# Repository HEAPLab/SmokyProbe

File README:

# SmokyProbe

Firmware
========

Project related to the firmware for the STM32-NUCLEO G071RB board, for sampling
the SmokyProbe on-board sensors via I2C.

SmokyProbe library (libsmokyprobe)
==================================

Host-side library for communicating with the STM32-NUCLEO board via serial interface.

Tools
=====

Host-side programs implementing specific reading functionalities.

Troubleshooting
===============

- If you have problems in tty communication with the device try the following
  stty settings:

	stty -F /dev/ttyACM0 -hupcl brkint ignpar -icrnl -ixon -opost -onlcr
	-isig -icanon -iexten -echo -echoe -echok -echoctl -echoke

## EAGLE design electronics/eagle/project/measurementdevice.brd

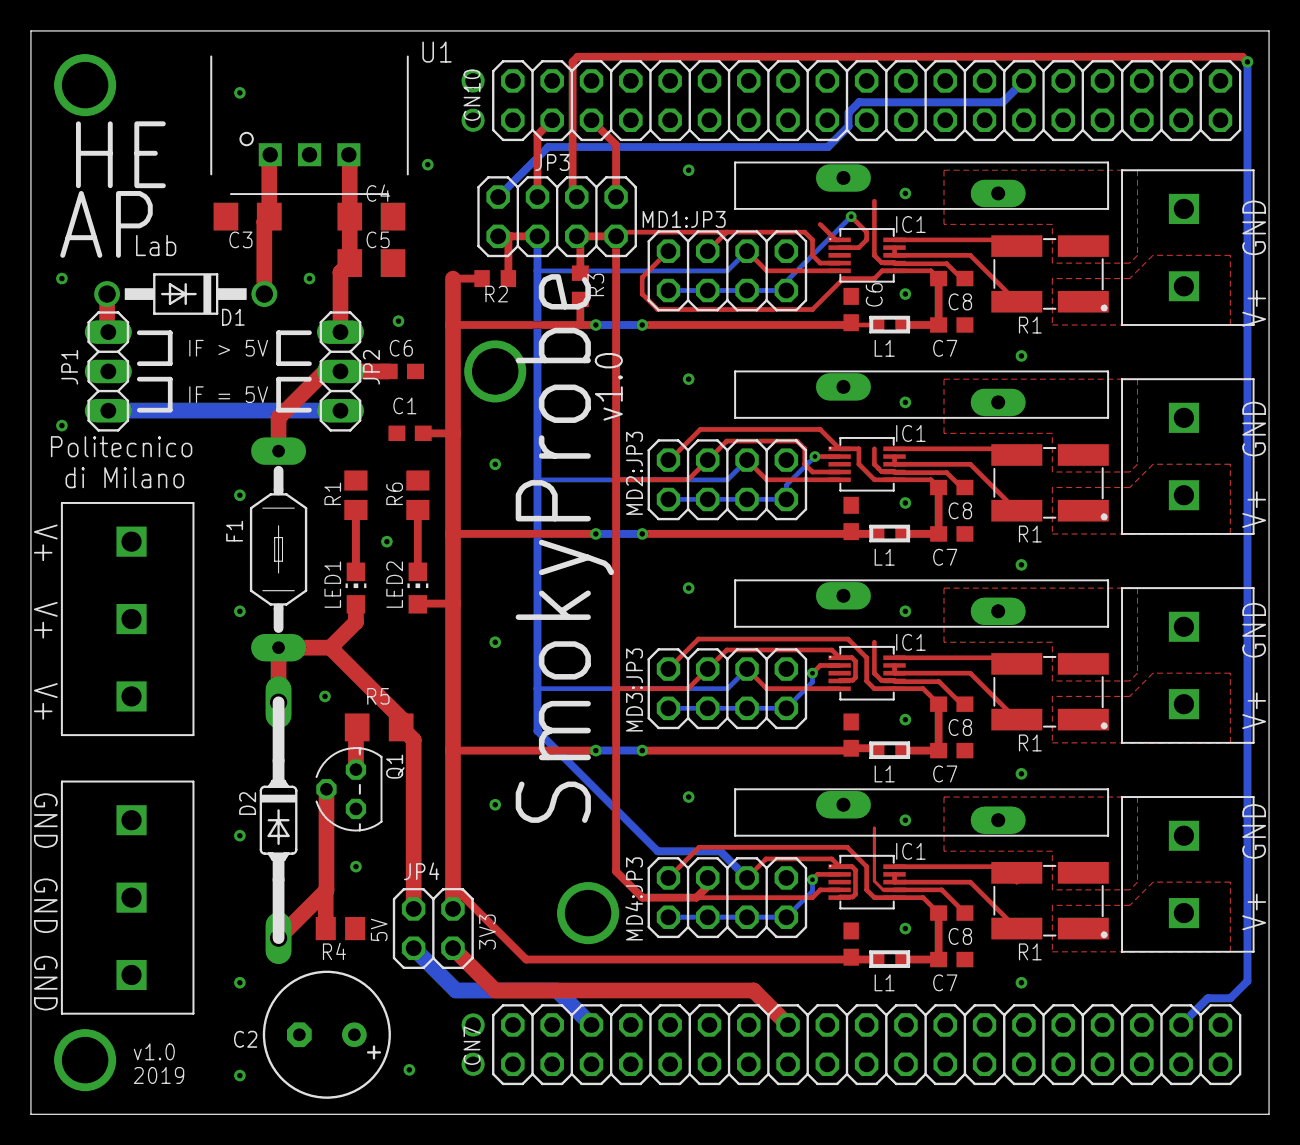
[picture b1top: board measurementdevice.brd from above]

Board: 4 copper layers, 80.0 x 70.0 mm, 63 parts (0 on the bottom side), 45 nets.

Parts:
C1: 1uF; C0603
C2: 100uF; E3,5-8
C3, C4, C5: 10uF; C1206
C6: 0.1uF; C0603
CN7, CN10: 2X19
D1: 1N5819; DO41-10
D2: BZD23C5V6; SOD81-ED
F1: 1.3A; LITTLEFUSE
JP1, JP2: 1X03
JP3: 2X04
JP4: 2X02
LED1, LED2: GREEN; CHIP-LED0805
MD1:C6, MD2:C6, MD3:C6, MD4:C6: 1uF; C0603
MD1:C7, MD2:C7, MD3:C7, MD4:C7: 0.1uF; C0603
MD1:C8, MD2:C8, MD3:C8, MD4:C8: 0.01uF; C0603
MD1:F1, MD2:F1, MD3:F1, MD4:F1: RUEF900
MD1:IC1, MD2:IC1, MD3:IC1, MD4:IC1: VSSOP10
MD1:JP3, MD2:JP3, MD3:JP3, MD4:JP3: 2X04
MD1:L1, MD2:L1, MD3:L1, MD4:L1: Ferrite Bead; 0603
MD1:R1, MD2:R1, MD3:R1, MD4:R1: 1224
MD1:X1, MD2:X1, MD3:X1, MD4:X1: PT1.5/3-50H-2
Q1: TN0604N3; TO-92
R1: 240; R0805
R2, R3: 3.9k; R0603
R4: 1k; R0805
R5: 5; R1206
R6: 100; R0805
U1: VX7805-1000; VX78-1000
X1, X2: PT1.5/3-50H-3

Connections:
3V3: CN7.16, JP4.3
+3V3: C1.2, JP4.4, LED2.A, MD1:C6.2, MD1:L1.N1, MD2:C6.2, MD2:L1.N1, MD3:C6.2, MD3:L1.N1, MD4:C6.2, MD4:L1.N1, R2.2, R3.2
+5V: D2.C, F1.2, JP4.2, LED1.A, R5.2
E5V: CN7.6, JP4.1
GND: C1.1, C2.-, C3.2, C4.2, C5.2, C6.2, CN7.8, CN7.19, CN7.20, CN7.22, CN10.9, CN10.20, MD1:C6.1, MD1:C7.1, MD1:C8.1, MD1:IC1.1, MD1:IC1.7, MD1:JP3.8, MD1:X1.P$1, MD2:C6.1, MD2:C7.1, MD2:C8.1, MD2:IC1.7, MD2:JP3.8, MD2:X1.P$1, MD3:C6.1, MD3:C7.1, MD3:C8.1, MD3:IC1.7, MD3:JP3.8, MD3:X1.P$1, MD4:C6.1, MD4:C7.1, MD4:C8.1, MD4:IC1.7, MD4:JP3.8, MD4:X1.P$1, Q1.1, R1.1, R4.1, R6.1, U1.P$2, X2.P$1, X2.P$2, X2.P$3
MD1:3V3_FILTERED: MD1:C7.2, MD1:C8.2, MD1:IC1.6, MD1:JP3.2, MD1:L1.N2
MD1:A0: MD1:IC1.2, MD1:JP3.1, MD1:JP3.3, MD1:JP3.5, MD1:JP3.7
MD1:PWR_IN: MD1:F1.P$2, MD1:R1.2
MD1:PWR_OUT: MD1:R1.1, MD1:X1.P$2
MD1:SENSE1: MD1:IC1.10, MD1:R1.3
MD1:SENSE2: MD1:IC1.8, MD1:IC1.9, MD1:R1.4
MD2:A0: MD2:IC1.2, MD2:JP3.1, MD2:JP3.3, MD2:JP3.5, MD2:JP3.7
MD2:PWR_IN: MD2:F1.P$2, MD2:R1.2
MD2:PWR_OUT: MD2:R1.1, MD2:X1.P$2
MD2:SENSE1: MD2:IC1.10, MD2:R1.3
MD2:SENSE2: MD2:IC1.8, MD2:IC1.9, MD2:R1.4
MD3:3V3_FILTERED: MD3:C7.2, MD3:C8.2, MD3:IC1.6, MD3:JP3.2, MD3:L1.N2
MD3:A0: MD3:IC1.2, MD3:JP3.1, MD3:JP3.3, MD3:JP3.5, MD3:JP3.7
MD3:PWR_IN: MD3:F1.P$2, MD3:R1.2
MD3:PWR_OUT: MD3:R1.1, MD3:X1.P$2
MD3:SENSE1: MD3:IC1.10, MD3:R1.3
MD3:SENSE2: MD3:IC1.8, MD3:IC1.9, MD3:R1.4
MD4:3V3_FILTERED: MD4:C7.2, MD4:C8.2, MD4:IC1.6, MD4:JP3.2, MD4:L1.N2
MD4:A0: MD4:IC1.2, MD4:JP3.1, MD4:JP3.3, MD4:JP3.5, MD4:JP3.7
MD4:PWR_IN: MD4:F1.P$2, MD4:R1.2
MD4:PWR_OUT: MD4:R1.1, MD4:X1.P$2
MD4:SENSE1: MD4:IC1.10, MD4:R1.3
MD4:SENSE2: MD4:IC1.8, MD4:IC1.9, MD4:R1.4
unnamed: C3.1, D1.C, U1.P$1
unnamed: D1.A, JP1.3
unnamed: LED1.C, R1.2
unnamed: JP1.1, JP2.1
unnamed: D2.A, Q1.2, R4.2
unnamed: C4.1, C5.1, JP2.3, U1.P$3
unnamed: LED2.C, R6.2
unnamed: Q1.3, R5.1
unnamed: C6.1, F1.1, JP2.2
unnamed: MD2:C7.2, MD2:C8.2, MD2:IC1.1, MD2:IC1.6, MD2:JP3.2, MD2:L1.N2
PB8: CN10.3, JP3.5
PB9: CN10.5, JP3.1
PB10: CN10.28, JP3.7
PB11: CN7.36, JP3.3
SCL: JP3.6, JP3.8, MD1:IC1.5, MD1:JP3.6, MD2:IC1.5, MD2:JP3.6, MD3:IC1.5, MD3:JP3.6, MD4:IC1.1, MD4:IC1.5, MD4:JP3.6, R2.1
SDA: JP3.2, JP3.4, MD1:IC1.4, MD1:JP3.4, MD2:IC1.4, MD2:JP3.4, MD3:IC1.1, MD3:IC1.4, MD3:JP3.4, MD4:IC1.4, MD4:JP3.4, R3.1
V+: C2.+, JP1.2, MD1:F1.P$1, MD2:F1.P$1, MD3:F1.P$1, MD4:F1.P$1, X1.P$1, X1.P$2, X1.P$3

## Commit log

2019-03-05 Initial import
2019-03-05 [Docs] Add a couple of STM32 documents
2019-03-06 [Electronics] Add EAGLE files
2019-03-06 [Docs] Add component datasheets
2019-03-06 Added gitignore file
2019-03-06 [Firmware] added project for nucleo-g071rb
2019-03-07 [Electronics] First RC for circuit
2019-04-19 [Electronics] Last version
2019-05-10 Updated firmware for CubeMX 5.2 and SW4STM32 2.9
2019-06-11 [Firmware] Refactoring with INA233 dedicated sources
    Using INA233_StatusCheck() function as diagnostic in the current main()
    implementation.
2019-06-11 [Firmware] INA233 HAL macro and var renaming
2019-06-11 [Firmware] INA233 manufacture info retrieval
2019-06-12 [Firmware] INA233 headers refactoring
    Three separate headers: configuration, data structures, function
    definitions.
2019-06-12 [Firmware] INA233 initialization function
2019-06-13 [Firmware] INA233 fixed calibration value
2019-06-13 [Firmware] INA233 implementation of V/I/P reading
2019-06-14 [Docs] Add first version of the manual
2019-06-18 [Firmware] Minor changes on code uniformity
2019-06-18 [Firmware] INA233: Configuration and reset in initialization
2019-06-18 [Firmware] INA233: Energy estimation first implementation
2019-06-20 [Firmware] main: test code in command interpreter style
2019-06-20 [Firmware] Minor changes
2019-06-20 [Firmware] INA233: sample count check in energy computation
2019-06-20 [Firmware] Timing for energy computing in milliseconds
2019-06-28 [Firmware] Fix LPUART configuration and init
2019-06-28 [Firmware] First host to device interaction
    Early implementation of a serial protocol based on a request/reply schema.
    The host sends request, and the device replies accordingly.
2019-07-11 [Firmware] INA233: Cosmetics
2019-07-12 [Firmware] Properly add timer resource from MXCube
2019-07-12 [Firmware] main: Rn_Interactive() by default
2019-07-12 [Firmware] INA233: Fixed energy computation
    * Fixed timer counter reset
    * Fixed average power consumption computation
2019-07-12 [Firmware] INA233: hostctrl.h macro refactoring
2019-07-12 [Firmware] Update project files
2019-07-12 [Firmware] INA233: InitThresholds / StatusCheck
2019-07-12 [Firmware] INA233: GetDeviceInfo refactoring
2019-07-12 [Firmware] INA233: main: testing modes
2019-07-25 [libsmokyprobe-dev] Low level library for device access
    Currently based on UART.
2019-07-25 [Firmware] INA233: remote volatile qualifier
2019-07-25 [Firmware] string length computation for device info
2019-07-25 [Firmware] Downscale UART baudrate
    Testing different combinations...
2019-07-25 [Firmware] Comment out minor code lines
2019-07-26 [libsmokyprobe-dev] Log messages revised
2019-07-26 [libsmokyprobe-dev] Add missing CMakeLists.txt
2019-07-26 [libsmokyprobe-dev] Add .gitignore
2019-07-26 [libsmokyprobe-dev] Review log4cpp default settings
2019-07-26 [libsmokyprobe-dev] Fix reply data char value comparison
2019-07-26 [libsmokyprobe-dev] Rename semaphore
2019-07-26 [Firmware] main: manage CHECK_DEVICE requests
2019-07-26 [Tools] smokytest: testing executable
2019-07-26 [libsmokyprobe-dev] Clean logger shutdown
2019-07-29 [Firmware] I2C addresses for channels [3-7]
2019-10-01 [Tools] smokytest: dirty refactoring for calibration session
    Print averaged voltage values.
2019-10-01 [libsmokyprobe-dev] smart_semaphore: remove return statement
2019-10-02 [Doc] Add serial fix to README
2019-10-02 [Tools] smokytest: new version
    Added select options to specify the measure to print out.
2019-11-29 Update docs
2020-03-13 [Tools] smokytest: Fixed wrong path for libsmokyprobe-dev
2020-06-15 [libsmokyprobe-dev/Firmware] Char based representation of protocol values
    This improves the readability of the debugging info.
2020-06-15 [libsmoskyprobe-dev] Refactoring of build and installation
2020-06-15 [Tools] Start reorganization in specific executable programs
2020-06-15 .gitignore: update
2020-06-15 [libsmokyprobe-dev] probe_uart: minor change
2020-06-15 [libsmokyprobe-dev] probe_uart: reply header receive check
    Valid header messages should be as long as MSG_REPLY_HEADER_LEN at least.
2020-06-16 [Firmware] Refactoring of variables scope
2020-06-16 [Firmware] Data transmission refactoring
    There are always data to sent. In case of error the data is represented
    by a string message.
2020-06-16 [Firmware] Run mode defined at compile-time
    * BATCH: print out lines with I/V/P and Vshunt values for all the channels
    * INTERACTIVE: command-responde mode
    * TESTS: test the UART port and the timing
2021-02-08 Transitional renaming of the initial libsmokyprobe
2021-02-08 Removed initial libsmokyprobe definition
2021-02-08 [libsmokyprobe] Renamed from -dev
2021-02-08 [README] Updated
2021-02-08 [Build] Root CMakeLists.txt added
2021-02-08 [libsmokyprobe] ProbeUART member functions refactoring
2021-02-08 Avoiding return codes equal to 0
2021-02-08 [libsmokyprobe] ProbeUART: revised log levels
2021-02-08 [libsmokyprobe] ProbeUART: return in case of construction error
2021-02-08 [Firmware] Reinitialize UART after each request/reply
2021-02-08 [libsmokyprobe] Review UART configuration parameters
2021-02-08 [Tools/Energy] Tools for energy consumption monitoring
    Start/stop of the energy consumption of the given set of channels.
2021-02-09 [libsmokyprobe] ProbeUART: flushing serial port buffers
2021-02-09 [libsmokyprobe] Minor reordering of ExitCode enum class
2021-02-09 [Tools] Remove deprecated 'smokytest'
2021-02-09 [Tools] Energy: revise start and stop option chars
2021-02-09 [Firmware] Fix status check function
2021-02-09 [Firmware] Added INA233_ClearFaults() function
2021-02-09 [Firmware] Function definitions in ina233_hal.h header
2021-02-09 [Firmware] Cosmetics
2021-02-09 Flash script shortcut
2021-02-09 [Tools] Remove deprecated 'monitor'
2021-02-09 [Tools] Energy: remove deprecated variable
2021-02-09 [Tools/Utils] Refactoring with utility library
2021-02-09 [libsmokyprobe] Minor CMake file improvements
2021-02-09 [Firmware] Project file update
    Not sure we need to track this.
2021-02-09 [Firmware] Binary file (release)
2021-02-09 [libsmokyprobe] Fix missing return statement
2021-02-15 [Firmware] Update number of channels to 8
2021-02-15 [Firmware] Redefine number slaves to 8
